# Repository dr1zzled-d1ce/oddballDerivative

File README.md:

# oddballDerivative: work in progress

This is my version of the Oddball. Atulloh was kind enough to send their personal kicad files to me.

I have no experience in KiCad or electronics whatsoever, so most of this was made possible due to a lot of generous people in the ergo community.

The major difference is that the thumb pcb has 3 keys instead of 2. The main pcb is pretty much untouched from the original.

Thanks to:
* atulloh/tullonator, for making the original Oddball
* u/Tweetydabirdie
* the Absolem Club
* the QMK discord
* the 40% Keyboards discord

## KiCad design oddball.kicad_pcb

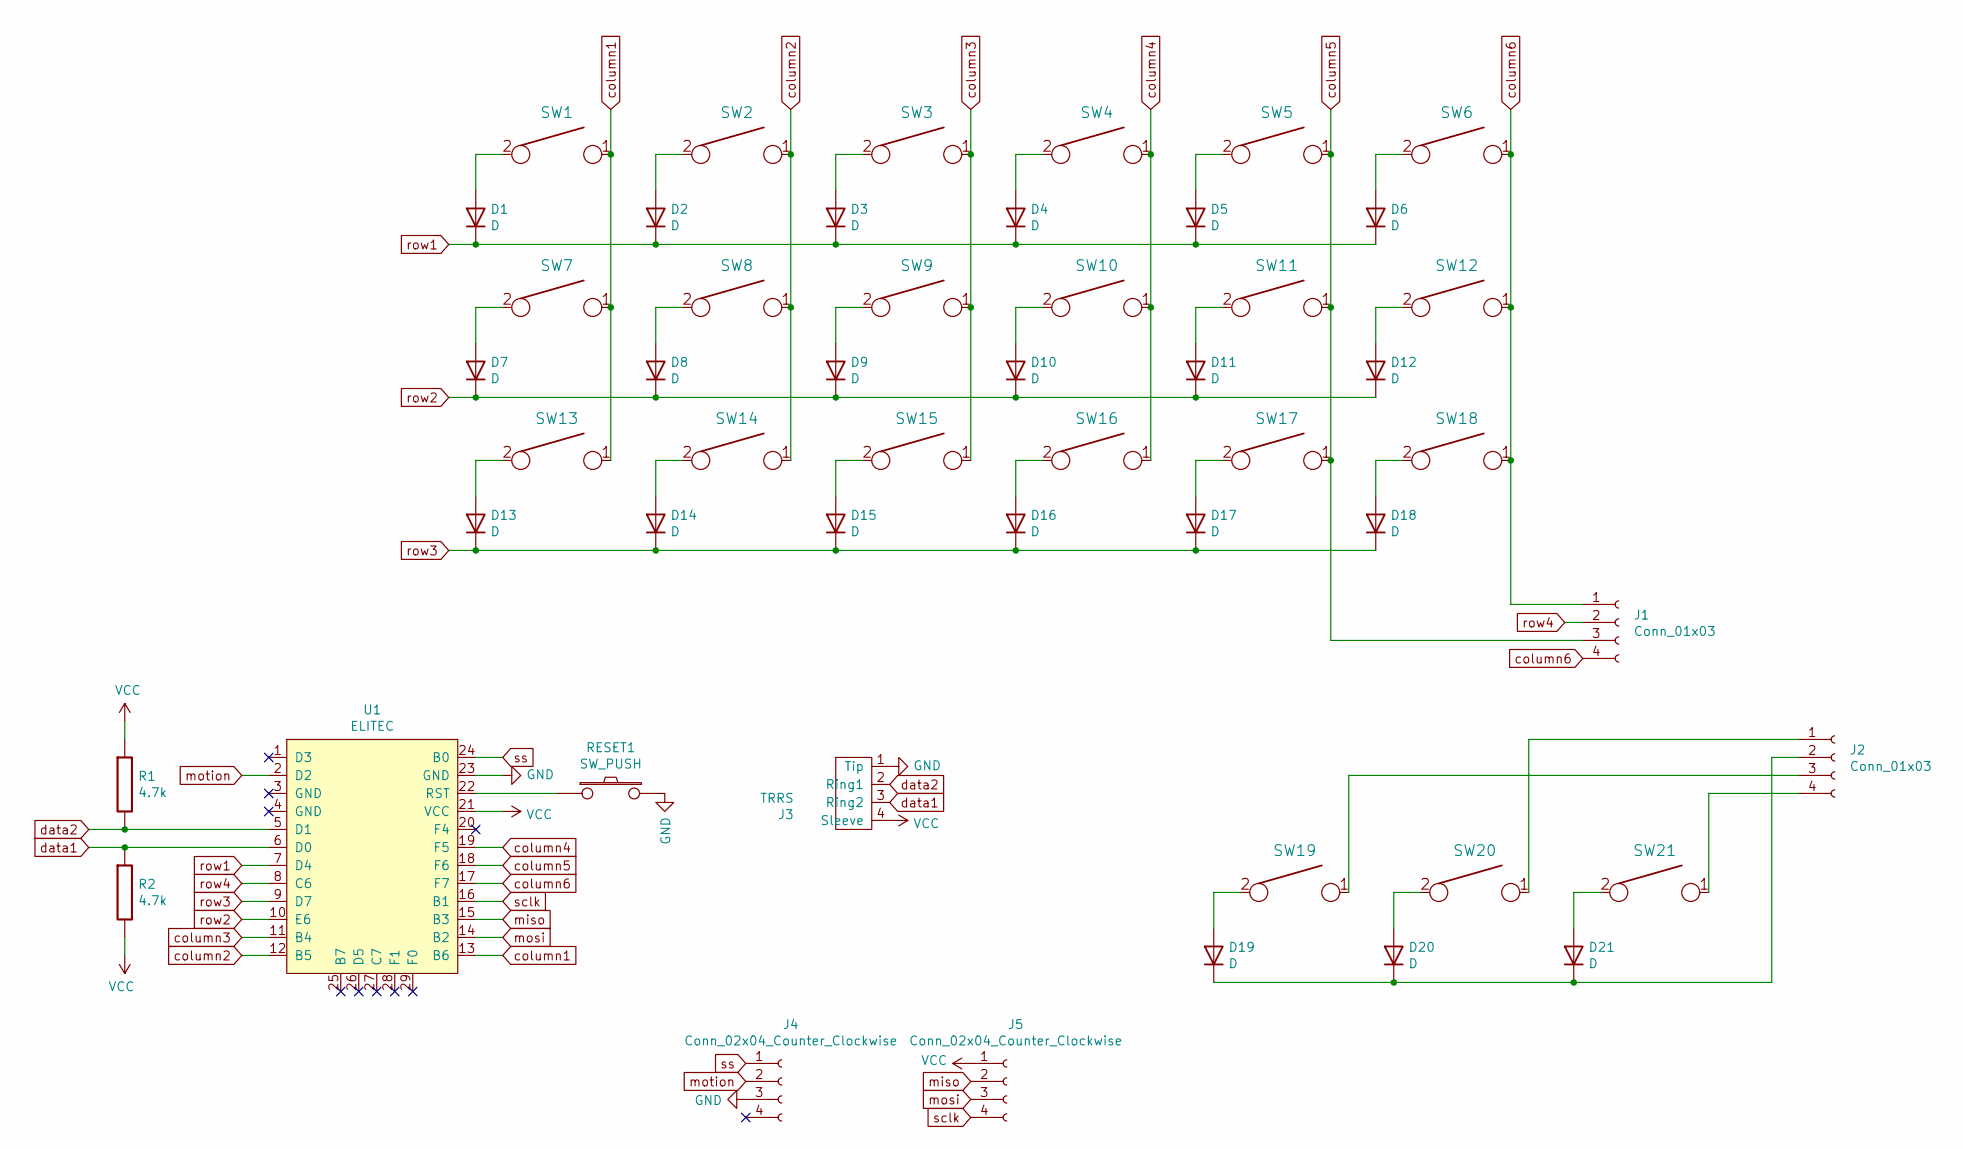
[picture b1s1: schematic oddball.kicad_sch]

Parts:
D1, D2, D3, D4, D5, D6, D7, D8, D9, D10, D11, D12, D13, D14, D15, D16, D17, D18, D19, D20, D21: D; Diode
J1, J2: Conn_01x03; PinSocket_1x04_P2.54mm_Vertical
J3: TRRS; TRRS-PJ-320A-dual
J4, J5: Conn_02x04_Counter_Clockwise; PinSocket_1x04_P2.54mm_Vertical
R1, R2: 4.7k; Resistor
RESET1: SW_PUSH; SW_Tactile_SPST_Angled_MJTP1117
SW1, SW2, SW3, SW4, SW5, SW6, SW7, SW8, SW9, SW10, SW11, SW12, SW13, SW14, SW15, SW16, SW17, SW18, SW19, SW20, SW21: KEYSW; Hybrid_PLATE_100H_Dual_hole-flip
U1: ELITEC; Elite-C

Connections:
GND: J3.1 (Tip), J4.3, RESET1.2, U1.23 (GND)
unnamed: D1.2 (A), SW1.2
unnamed: D2.2 (A), SW2.2
unnamed: D3.2 (A), SW3.2
unnamed: D4.2 (A), SW4.2
unnamed: D5.2 (A), SW5.2
unnamed: D6.2 (A), SW6.2
unnamed: D7.2 (A), SW7.2
unnamed: D8.2 (A), SW8.2
unnamed: D9.2 (A), SW9.2
unnamed: D10.2 (A), SW10.2
unnamed: D11.2 (A), SW11.2
unnamed: D12.2 (A), SW12.2
unnamed: D13.2 (A), SW13.2
unnamed: D14.2 (A), SW14.2
unnamed: D15.2 (A), SW15.2
unnamed: D16.2 (A), SW16.2
unnamed: D17.2 (A), SW17.2
unnamed: D18.2 (A), SW18.2
unnamed: D19.2 (A), SW19.2
unnamed: D19.1 (K), D20.1 (K), D21.1 (K), J2.2
unnamed: D20.2 (A), SW20.2
unnamed: D21.2 (A), SW21.2
unnamed: J2.1, SW20.1
unnamed: J2.3, SW19.1
unnamed: J2.4, SW21.1
unnamed: RESET1.1, U1.22 (RST)
VCC: J3.4 (Sleeve), J5.1, R1.1, R2.2, U1.21 (VCC)
column1: SW1.1, SW7.1, SW13.1, U1.13 (B6)
column2: SW2.1, SW8.1, SW14.1, U1.12 (B5)
column3: SW3.1, SW9.1, SW15.1, U1.11 (B4)
column4: SW4.1, SW10.1, SW16.1, U1.19 (F5)
column5: J1.3, SW5.1, SW11.1, SW17.1, U1.18 (F6)
column6: J1.1, J1.4, SW6.1, SW12.1, SW18.1, U1.17 (F7)
data1: J3.3 (Ring2), R2.1, U1.6 (D0)
data2: J3.2 (Ring1), R1.2, U1.5 (D1)
miso: J5.2, U1.15 (B3)
mosi: J5.3, U1.14 (B2)
motion: J4.2, U1.2 (D2)
row1: D1.1 (K), D2.1 (K), D3.1 (K), D4.1 (K), D5.1 (K), D6.1 (K), U1.7 (D4)
row2: D7.1 (K), D8.1 (K), D9.1 (K), D10.1 (K), D11.1 (K), D12.1 (K), U1.10 (E6)
row3: D13.1 (K), D14.1 (K), D15.1 (K), D16.1 (K), D17.1 (K), D18.1 (K), U1.9 (D7)
row4: J1.2, U1.8 (C6)
sclk: J5.4, U1.16 (B1)
ss: J4.1, U1.24 (B0)

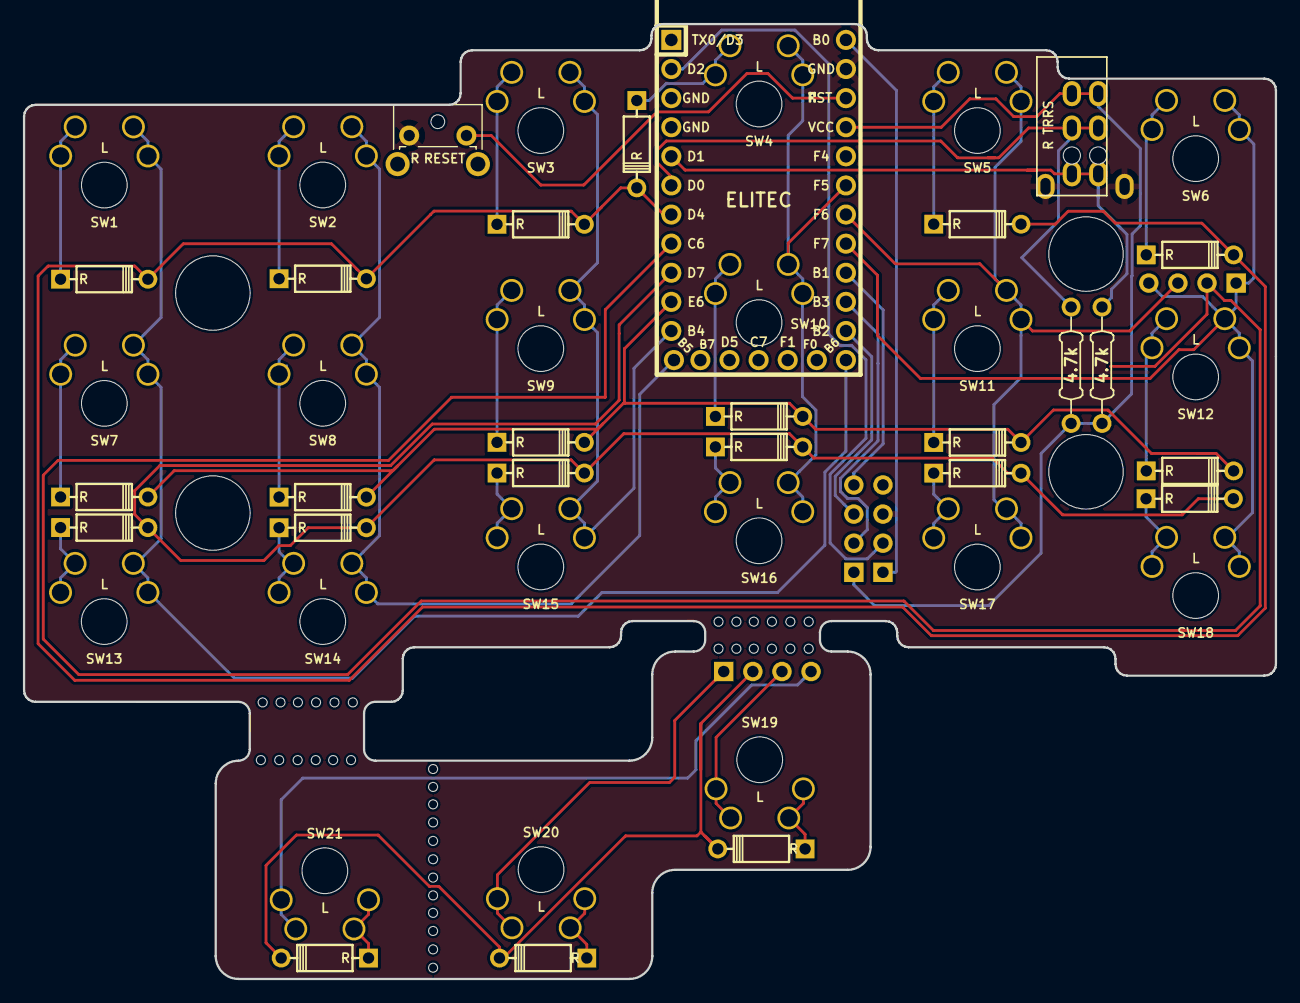
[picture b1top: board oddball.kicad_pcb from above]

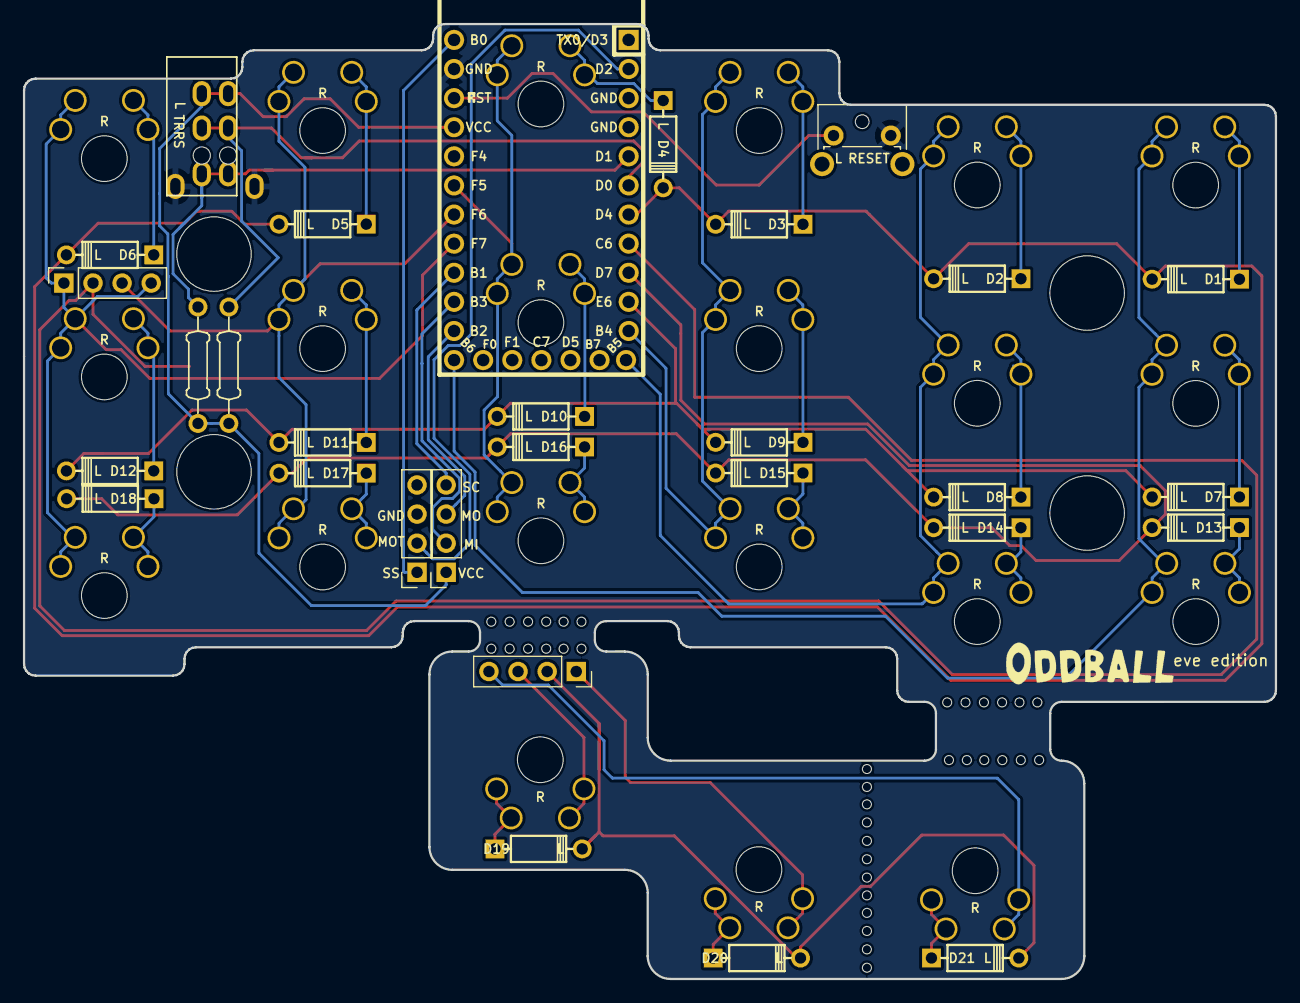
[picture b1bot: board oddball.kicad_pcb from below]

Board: 2 copper layers, 109.3 x 83.3 mm, 55 parts (26 on the bottom side), 45 nets.

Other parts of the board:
U4, U4#2, U4#3, U4#4: HOLE; Mount

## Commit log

2023-08-07 simple panel
2023-08-08 move the bites to the right plcae
